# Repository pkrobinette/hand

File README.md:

# Myolectric Control of Prosthetics and Robotics via Machine Learning Interpretation
This library is used for research on the myoelectric control of prosthetics and robotics via machine learning interpretation. In an effort to increase the functionality of prosthetic and robotics, this research focuses on increasing dexterity by identifying/classifying individual finger movements, a challenge due to the interconnected nature of the muscles of the forearm and the noninvasive nature of electrodes.

A myoelectric signal (MES) is a voltage difference measured across two muscles as shown in the figure below. The two electrodes across the muscles of the forearm are measuring the MES and the third electrode across the boney part of the elbow is used to ground the signal.

The signals from the electrodes on the arm are then read by a PCB which takes the differential voltage, or MES, filters the signal, and amplifies the signal to be read by an Arduino. A diagram of the circuit is on the left which shows the components of the circuit and their functions. The physical PCB is pictured on the right.

The amplified MES from the PCB is then read into an Arduino which controls the 3D printed hand by triggering attached servos. Once activated, the servos rotate, pulling their attached strings which are run the 3D printed hand's fingers like tendons, and closing the hand into a fist. Once activated again, the servos rotate back, releasing the tension in their strings and allowing the hand to open again. The figure below shows the 3D printed hand and the servos attached on the back.

Previous research has accomplished the response of the hand to opening and closing, and the results can be seen [here.](https://www.youtube.com/watch?v=ljKoZNYS_Rw) This research works to improve upon this past model by implementing control for individual fingers.

## [Circuit](https://github.com/pkrobinette/hand/tree/main/Circuit)
- KiCAD files for the PCB with surface mounted components used in this research.

## [Data](https://github.com/pkrobinette/hand/tree/main/Data)
- Houses the data used in the analysis of individual finger movements. Signals are recorded for 7 different gestures:
  - **null** (no movement)
  - **fist** open and close
  - **thumb** open and close
  - **index** open and close
  - **middle** open and close
  - **ring** open and close
  - **pinkie** open and close

## [Scripts](https://github.com/pkrobinette/hand/tree/main/Scripts)
- Houses the files that extract `Data`. The extracted features from the data can either be combined into one file or sorted into seperate files based on their labels. The extracted features are then implemented and tested on various ml supervised learning models.

## [Results](https://github.com/pkrobinette/hand/tree/main/Results)
- Contains Confusion Matrix images for the various ml models implemented and tested. 

**Acknowledgements** Presbyterian College Department of Physics, NASA SC Space Grant Consortium, SC-INBRE, SCICU

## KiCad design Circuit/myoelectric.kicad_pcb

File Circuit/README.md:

# Circuit

This circuit is made using KiCAD. To access the schematic, open `myoelectric.pro` in KiCAD. The other files
will be accessible in the KiCAD software by opening this one file.

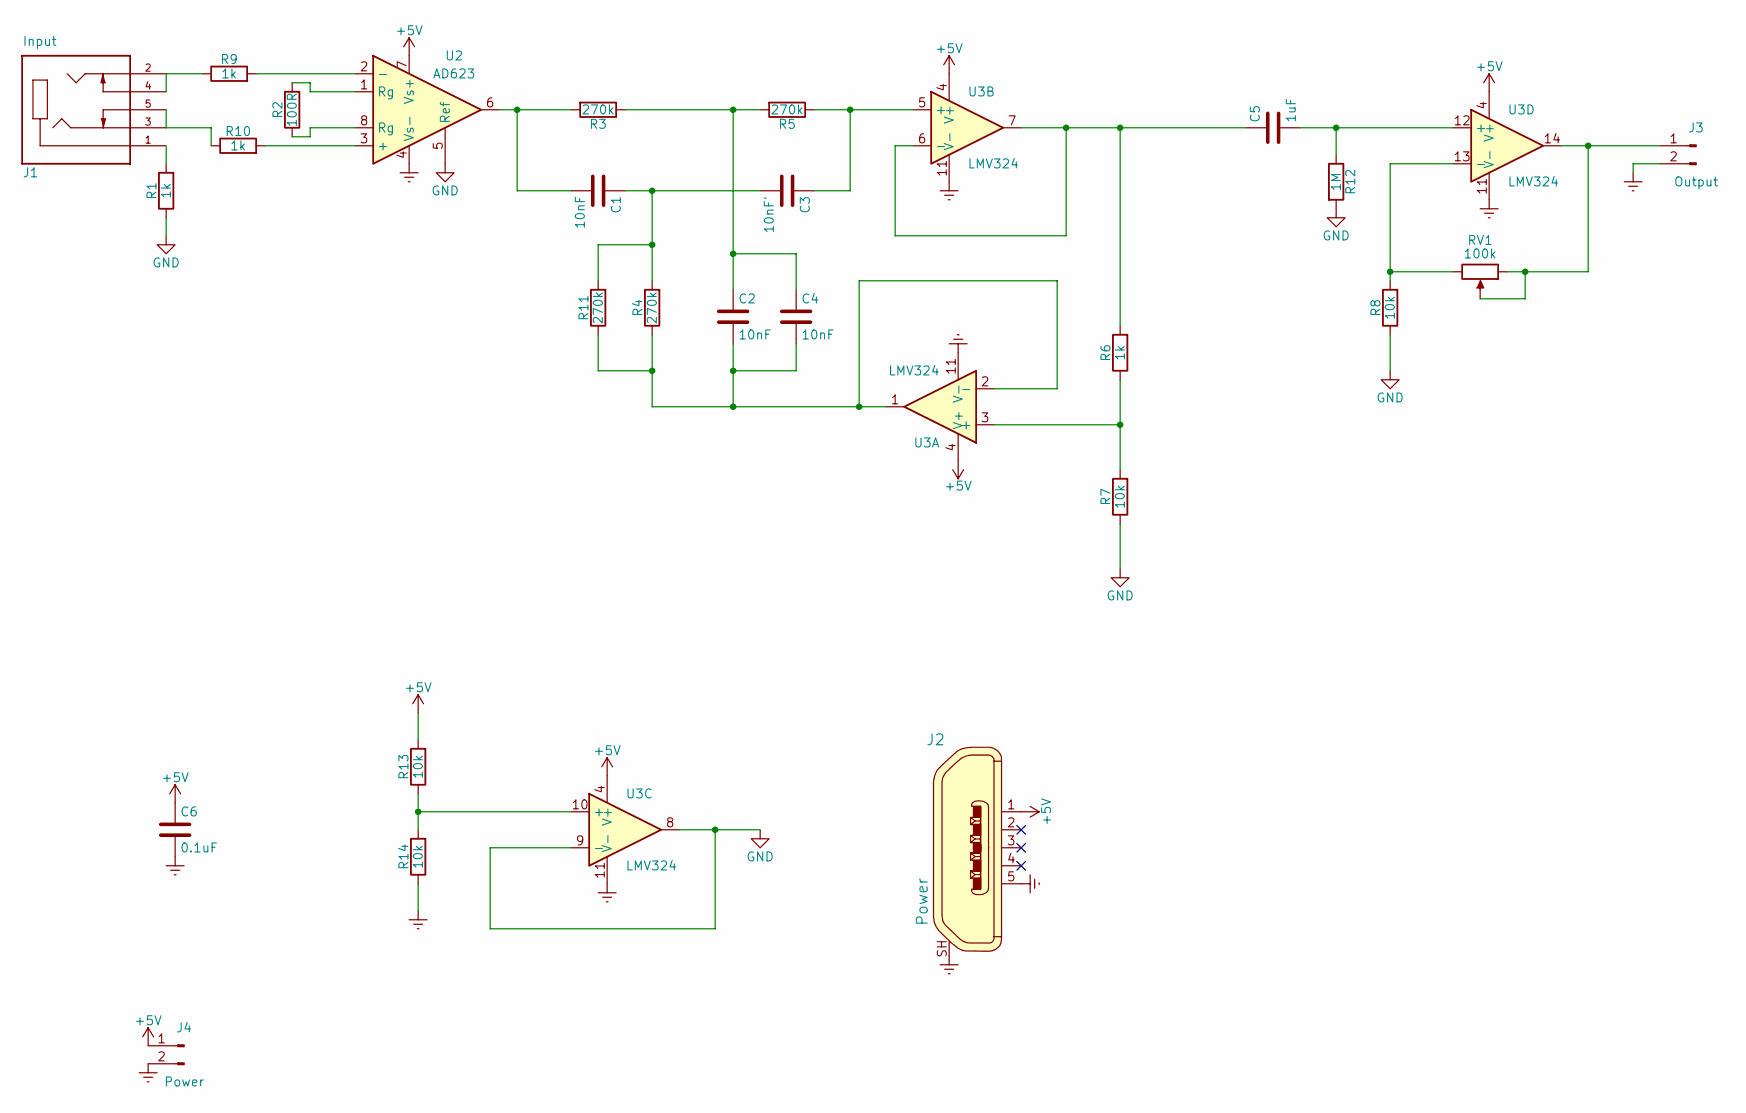
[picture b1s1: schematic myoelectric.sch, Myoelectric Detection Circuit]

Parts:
C1, C2, C4: 10nF; C_1206
C3: 10nF'; C_1206
C5: 1uF; C_Disc_D5.0mm_W2.5mm_P5.00mm
C6: 0.1uF; C_Disc_D5.0mm_W2.5mm_P5.00mm
J1: Input; CUI_SJ1-3535N
J2: Power; USB_Micro_B_Female_10118194-0001LF; MPN 10118194-0001LF; Digi-Key_PN 609-4618-1-ND
J3: Output; Pin_Header_Straight_1x02_Pitch2.54mm
J4: Power; Pin_Header_Straight_1x02_Pitch2.54mm
R1, R6, R9, R10: 1k; R_1206
R2: 100R; R_1206
R3, R4, R5, R11: 270k; R_1206
R7, R8, R13, R14: 10k; R_1206
R12: 1M; R_1206
RV1: 100k; Potentiometer_Trimmer_Bourns_3266Y
U2: AD623; SOIC-8_3.9x4.9mm_Pitch1.27mm
U3: LMV324; SOIC-14_3.9x8.7mm_Pitch1.27mm

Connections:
+5V: C6.1, J2.1, J4.1, R13.2, U2.7 (Vs+), U3.4 (V+)
Earth: C6.2, J2.5, J2.SH, J3.2, J4.2, R14.1, U2.4 (Vs-), U3.11 (V-)
GND: R1.1, R7.1, R8.1, R12.2, U2.5 (Ref), U3.8, U3.9 (-)
unnamed: C1.1, C3.2, R4.2, R11.2
unnamed: C1.2, R3.2, U2.6
unnamed: C2.1, C4.1, R3.1, R5.2
unnamed: C2.2, C4.2, R4.1, R11.1, U3.1, U3.2 (-)
unnamed: C3.1, R5.1, U3.5 (+)
unnamed: C5.1, R6.2, U3.6 (-), U3.7
unnamed: C5.2, R12.1, U3.12 (+)
unnamed: J1.1, R1.2
unnamed: J1.2, J1.4, R9.1
unnamed: J1.3, J1.5, R10.1
unnamed: J3.1, RV1.1, RV1.2, U3.14
unnamed: R2.1, U2.8 (Rg)
unnamed: R2.2, U2.1 (Rg)
unnamed: R6.1, R7.2, U3.3 (+)
unnamed: R8.2, RV1.3, U3.13 (-)
unnamed: R9.2, U2.2 (-)
unnamed: R10.2, U2.3 (+)
unnamed: R13.1, R14.2, U3.10 (+)

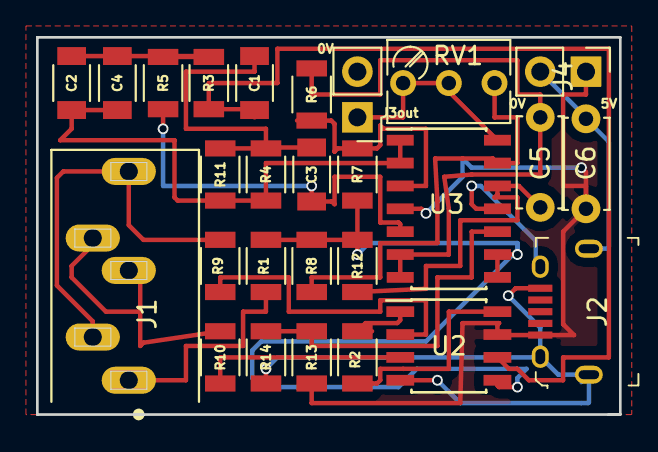
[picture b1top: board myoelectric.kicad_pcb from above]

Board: 2 copper layers, 32.4 x 21.0 mm, 27 parts (0 on the bottom side), 21 nets.

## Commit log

2020-11-17 upload files
2020-11-17 Rename Code/Algorithms5_13.py to Scripts/Algorithms5_13.py
2020-11-17 Rename Code/combinedFeatureExtraction.py to Scripts/combinedFeatureExtraction.py
2020-11-17 Rename Code/separateFeatureExtraction.py to Scripts/separateFeatureExtraction.py
2020-11-17 Rename Algorithms5_13.py to gen_ml_models.py
2020-11-18 circuit pictures
2020-11-18 prosthetic hand image
2020-11-18 images
2020-11-18 Updated output data files
2020-11-18 features image
2020-11-18 circuit redo
2020-11-18 myo pro file
